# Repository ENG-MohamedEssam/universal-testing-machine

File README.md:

# universal-testing-machine

## **Abstract**
#### This projet at first was about Reverse-Engineering a Stress/Strain analysis machine, then fix it and Automate it's process.
#### The following is an image of the machine 

#### Every part of the machine was Reverse-Engineered from the boards to the hydraulics to the classic control.
#### The following is an image of one of the Reverse-Engineered boards which was mine to Reverese-Engineer.

#### I reverse Engineered The MV3058

#### Due to financial and permits issues the project was turned to be a prototype working with Embedded Systems.

#### The following is an image of the Prototype

#### The boards were desiged as follows, one board for the control, the second as a relay module. 

## **How the prototype works?**
 
#### The prototype mainly does exactly what the original machine does but on a smaller scale.
#### we mainly put a specimen between the two grippers and the machine puts tension or compression on the specimen till it breaks 
#### then it draws the Stress/Strain curves of the specimen's material.
#### It has a stepper motor used to adjust the place of the speciment, 
#### a piston that's derived by a hydraulic pump, 
#### a gripper used to grab the specimen.
#### As far as the Embedded systems part is concerend the machine had mainly 2 sensors ,
#### The Load Cell that's used to measure the Force and the Linear potentiometer that's used to measer the delta L.
#### the prototype is based mainly on two equations, Stress equation and Strain equation.
#### σ = F/A   ,    ε = δ/L  
#### the only two variables in these equations are the Force and the change in the length 

#### The following is images of the boards and panel.

#### The follwing is Single Line Diagram that was made by me , it'll give you a good overview of all the Hardware connections in the panel

#### The following link has some small SolidWorks parts that i've made for the machine whether it was as a specimen or for the sensors housings 
#### [parts](https://github.com/ENG-MohamedEssam/universal-testing-machine/tree/main/other-files/parts)

#### The following link has an explanation of the Embedded systems part explained by me 
#### [Explanation](https://drive.google.com/file/d/1bGaOVOjb-tQGSpPLI7ITkfYBf-VQDN8E/view)

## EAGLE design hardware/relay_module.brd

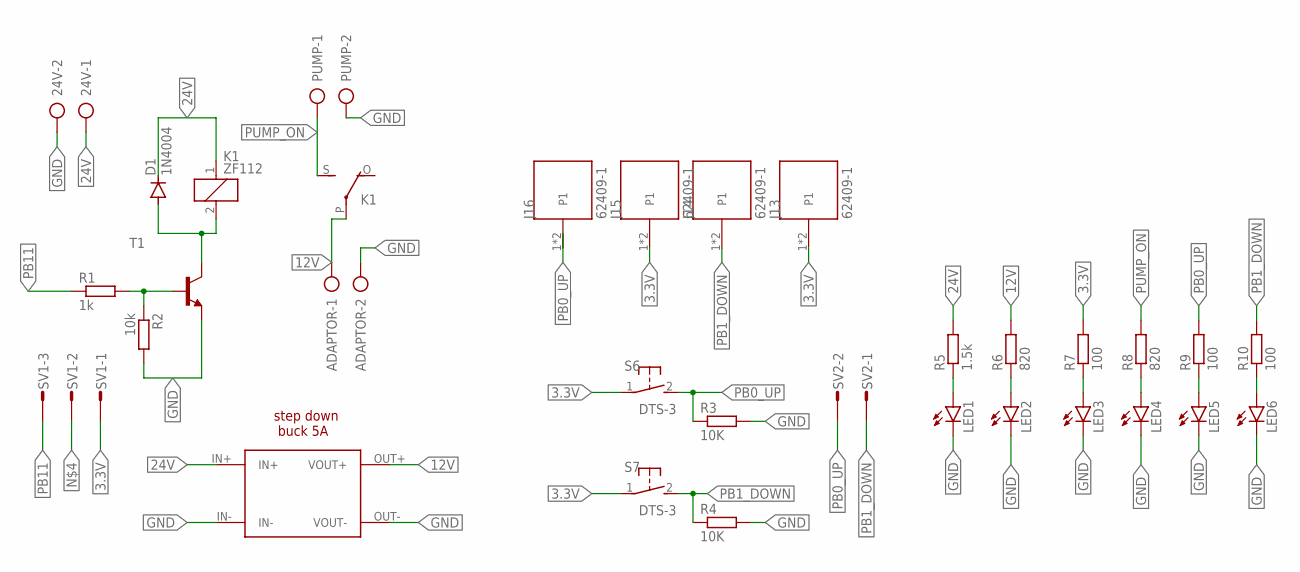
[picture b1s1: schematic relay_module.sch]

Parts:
24V: AK300/2
ADAPTOR: AK300/2
D1: 1N4004; DO41-10
J13, J14, J15, J16: 62409-1; TE_62409-1
K1: ZF112
LED1, LED2, LED3, LED4, LED5, LED6: LED5MM
PUMP: AK300/2
R1: 1k; 0204/7
R2: 10k; 0204/7
R3, R4: 10K; 0204/7
R5: 1.5k; 0204/7
R6, R8: 820; 0204/7
R7, R9, R10: 100; 0204/7
S6, S7: DTS-3
SV1: CON-AMP-MT_S03P
SV2: CON-AMP-MT_S02P
T1: 2N2222-NPN-TO92-EBC; TO92-EBC
U$1: BUCK_5A

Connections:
3.3V: J13.1, J13.2, J15.1, J15.2, R7.2, S6.1, S7.1, SV1.1
12V: ADAPTOR.1, K1.P, R6.2, U$1.OUT+ (VOUT+)
24V: 24V.1, D1.C, K1.1, R5.2, U$1.IN+
GND: 24V.2, ADAPTOR.2, LED1.K (C), LED2.K (C), LED3.K (C), LED4.K (C), LED5.K (C), LED6.K (C), PUMP.2, R2.2, R3.2, R4.2, T1.E, U$1.IN-, U$1.OUT- (VOUT-)
unnamed: R1.2, R2.1, T1.B
unnamed: LED1.A, R5.1
unnamed: D1.A, K1.2, T1.C
unnamed: LED2.A, R6.1
unnamed: LED5.A, R9.1
unnamed: LED3.A, R7.1
unnamed: LED4.A, R8.1
unnamed: LED6.A, R10.1
PB0_UP: J16.1, J16.2, R3.1, R9.2, S6.2, SV2.2
PB1_DOWN: J14.1, J14.2, R4.1, R10.2, S7.2, SV2.1
PB11: R1.1, SV1.3
PUMP_ON: K1.S, PUMP.1, R8.2

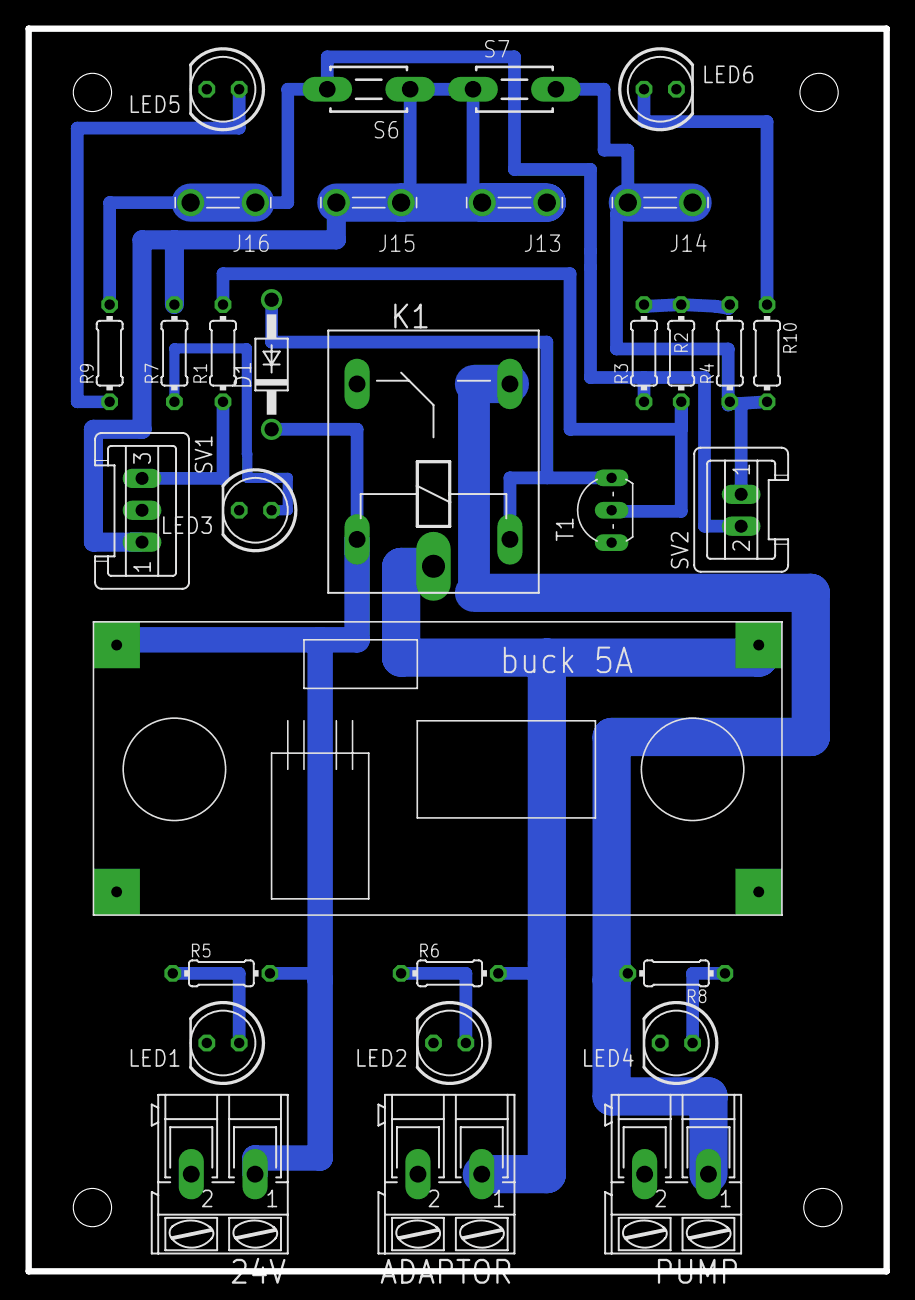
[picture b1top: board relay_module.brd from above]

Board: 2 copper layers, 67.3 x 97.5 mm, 31 parts (0 on the bottom side), 16 nets.

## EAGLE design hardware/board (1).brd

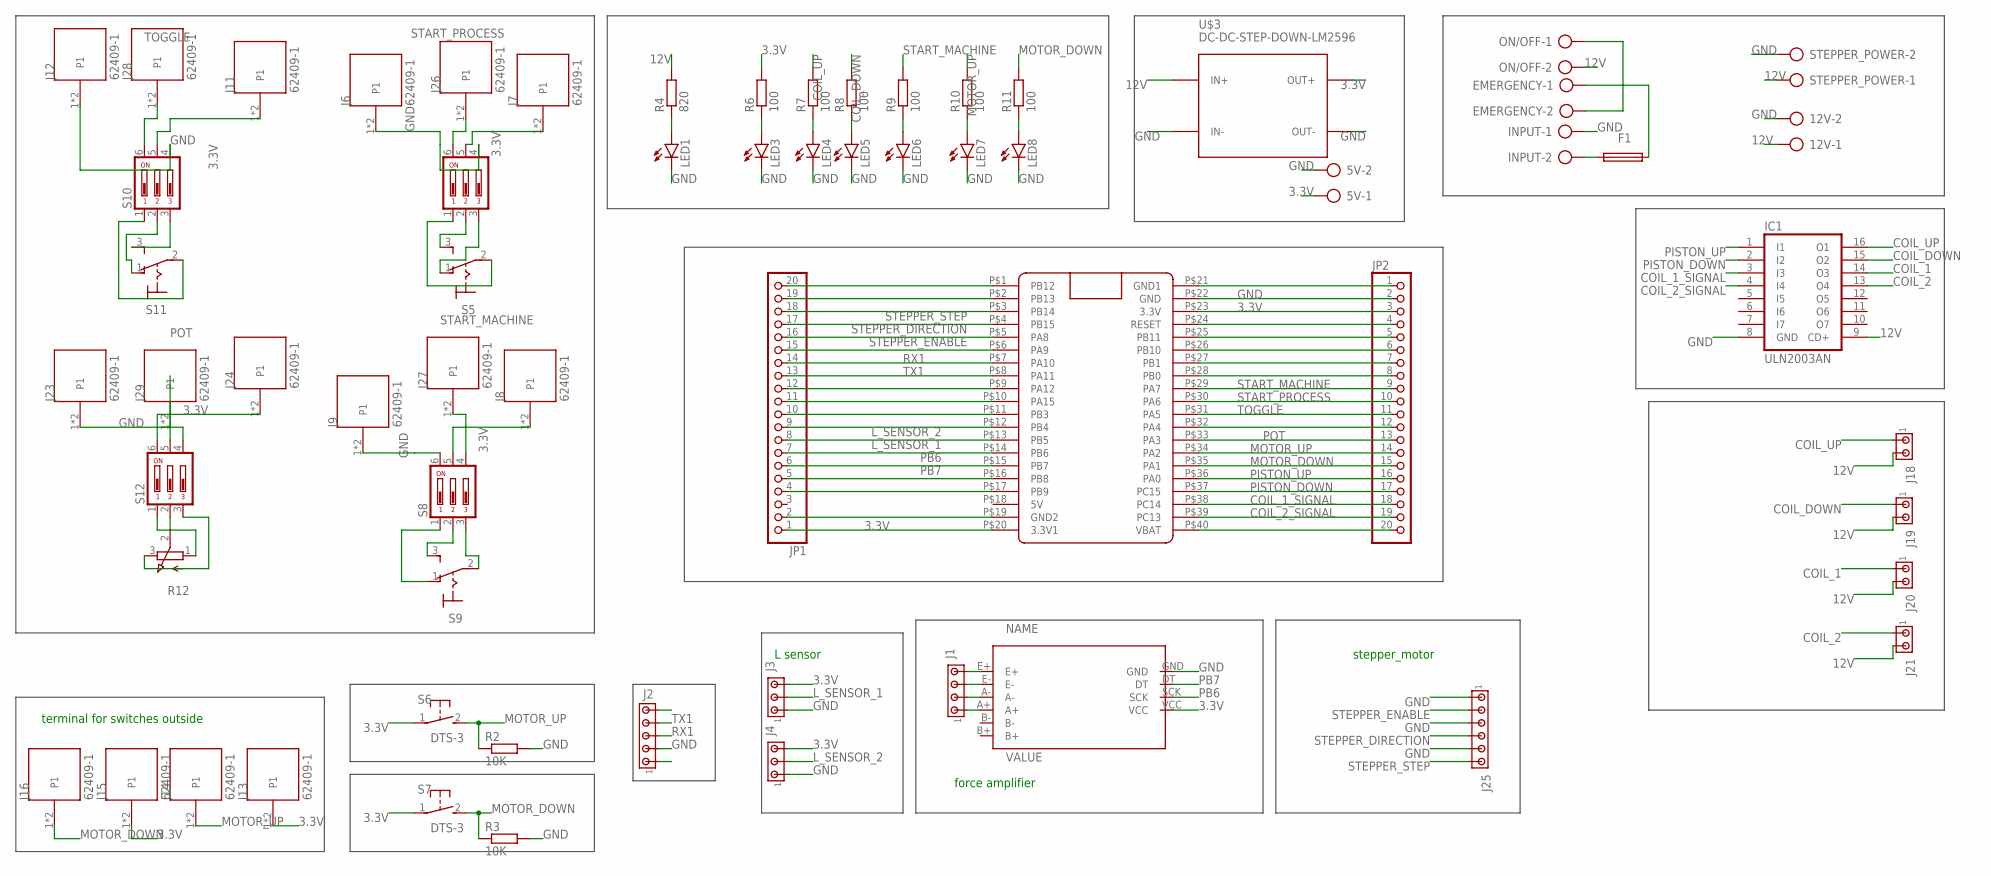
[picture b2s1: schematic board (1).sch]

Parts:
5V, 12V: AK300/2
EMERGENCY: AK300/2
F1: SH22
IC1: ULN2003AN; DIL16
INPUT: AK300/2
J1: MTA04-100; 10X04MTA
J2: MTA05-100; 10X05MTA
J3, J4: MTA03-100; 10X03MTA
J6, J7, J8, J9, J11, J12, J13, J14, J15, J16, J23, J24, J26, J27, J28, J29: 62409-1; TE_62409-1
J18, J19, J20, J21: MTA02-100; 10X02MTA
J25: MTA06-100; 10X06MTA
JP1, JP2: PINHD-1X20; 1X20
LED1, LED3, LED4, LED5, LED6, LED7, LED8: LED3MM
ON/OFF: AK300/2
R2, R3: 10K; 0204/7
R4: 820; 0204/7
R6, R7, R8, R9, R10, R11: 100; 0204/7
R12: 3RP/1610N
S4, S8, S10, S12: DP03; DP-03
S5, S9, S11: 320-916
S6, S7: DTS-3
STEPPER_POWER: AK300/2
U$1: BLUE_PILL
U$2: HX711A; HX711
U$3: DC-DC-STEP-DOWN-LM2596

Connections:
3.3V: 5V.1, J3.3, J4.3, J7.1, J7.2, J8.1, J8.2, J11.1, J11.2, J13.1, J13.2, J15.1, J15.2, J24.1, J24.2, JP1.1, JP2.3, R6.2, S4.5, S6.1, S7.1, S8.5, S10.5, S12.6, U$1.P$20 (3.3V1), U$1.P$23 (3.3V), U$2.VCC, U$3.OUT+
12V: 12V.1, IC1.9 (CD+), J18.2, J19.2, J20.2, J21.2, ON/OFF.2, R4.2, STEPPER_POWER.1, U$3.IN+
COIL_1: IC1.14 (O3), J20.1
COIL_1_SIGNAL: IC1.3 (I3), JP2.18, U$1.P$38 (PC14)
COIL_2: IC1.13 (O4), J21.1
COIL_2_SIGNAL: IC1.4 (I4), JP2.19, U$1.P$39 (PC13)
COIL_DOWN: IC1.15 (O2), J19.1, R8.2
COIL_UP: IC1.16 (O1), J18.1, R7.2
GND: 5V.2, 12V.2, IC1.8 (GND), INPUT.1, J2.2, J3.1, J4.1, J6.1, J6.2, J9.1, J9.2, J12.1, J12.2, J23.1, J23.2, J25.1, J25.3, J25.5, JP1.2, JP2.2, LED1.K (C), LED3.K (C), LED4.K (C), LED5.K (C), LED6.K (C), LED7.K (C), LED8.K (C), R2.2, R3.2, S4.4, S8.6, S10.4, S12.4, STEPPER_POWER.2, U$1.P$19 (GND2), U$1.P$22 (GND), U$2.GND, U$3.IN-, U$3.OUT-
L_SENSOR_1: J3.2, JP1.8, U$1.P$13 (PB5)
L_SENSOR_2: J4.2, JP1.9, U$1.P$12 (PB4)
MOTOR_DOWN: J16.1, J16.2, JP2.15, R3.1, R11.2, S7.2, U$1.P$35 (PA1)
MOTOR_UP: J14.1, J14.2, JP2.14, R2.1, R10.2, S6.2, U$1.P$34 (PA2)
unnamed: J1.4, U$2.E+
unnamed: J1.3, U$2.E-
unnamed: J1.2, U$2.A-
unnamed: J1.1, U$2.A+
unnamed: LED1.A, R4.1
unnamed: LED3.A, R6.1
unnamed: LED4.A, R7.1
unnamed: LED5.A, R8.1
unnamed: LED6.A, R9.1
unnamed: LED7.A, R10.1
unnamed: LED8.A, R11.1
unnamed: F1.1, INPUT.2
unnamed: S4.1, S5.2
unnamed: S4.2, S5.3 (S)
unnamed: JP1.4, U$1.P$17 (PB9)
unnamed: JP1.5, U$1.P$16 (PB8)
unnamed: JP1.10, U$1.P$11 (PB3)
unnamed: JP1.11, U$1.P$10 (PA15)
unnamed: JP1.12, U$1.P$9 (PA12)
unnamed: JP1.13, U$1.P$8 (PA11)
unnamed: EMERGENCY.1, F1.2
unnamed: EMERGENCY.2, ON/OFF.1
unnamed: JP2.20, U$1.P$40 (VBAT)
unnamed: JP2.7, U$1.P$27 (PB1)
unnamed: JP2.8, U$1.P$28 (PB0)
unnamed: JP1.20, U$1.P$1 (PB12)
unnamed: JP1.19, U$1.P$2 (PB13)
unnamed: S4.3, S5.1 (O)
unnamed: S10.1, S11.2
unnamed: S8.3, S9.2
unnamed: S8.1, S9.1 (O)
unnamed: JP2.1, U$1.P$21 (GND1)
unnamed: JP2.4, U$1.P$24 (RESET)
unnamed: S8.2, S9.3 (S)
unnamed: S10.3, S11.3 (S)
unnamed: S10.2, S11.1 (O)
unnamed: JP2.6, U$1.P$26 (PB10)
unnamed: R12.3 (E), S12.3
unnamed: R12.1 (A), S12.1
unnamed: R12.2 (S), S12.2
unnamed: JP2.12, U$1.P$32 (PA4)
unnamed: JP2.5, U$1.P$25 (PB11)
PB6: JP1.7, U$1.P$14 (PB6), U$2.SCK
PB7: JP1.6, U$1.P$15 (PB7), U$2.DT
PISTON_DOWN: IC1.2 (I2), JP2.17, U$1.P$37 (PC15)
PISTON_UP: IC1.1 (I1), JP2.16, U$1.P$36 (PA0)
POT: J29.1, J29.2, JP2.13, S12.5, U$1.P$33 (PA3)
RX1: J2.3, JP1.15, U$1.P$6 (PA9)
START_MACHINE: J27.1, J27.2, JP2.9, R9.2, S8.4, U$1.P$29 (PA7)
START_PROCESS: J26.1, J26.2, JP2.10, S4.6, U$1.P$30 (PA6)
STEPPER_DIRECTION: J25.4, JP1.17, U$1.P$4 (PB15)
STEPPER_ENABLE: J25.2, JP1.16, U$1.P$5 (PA8)
STEPPER_STEP: J25.6, JP1.18, U$1.P$3 (PB14)
TOGGLE: J28.1, J28.2, JP2.11, S10.6, U$1.P$31 (PA5)
TX1: J2.4, JP1.14, U$1.P$7 (PA10)

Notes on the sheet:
force amplifier
stepper_motor
L sensor
terminal for switches outside

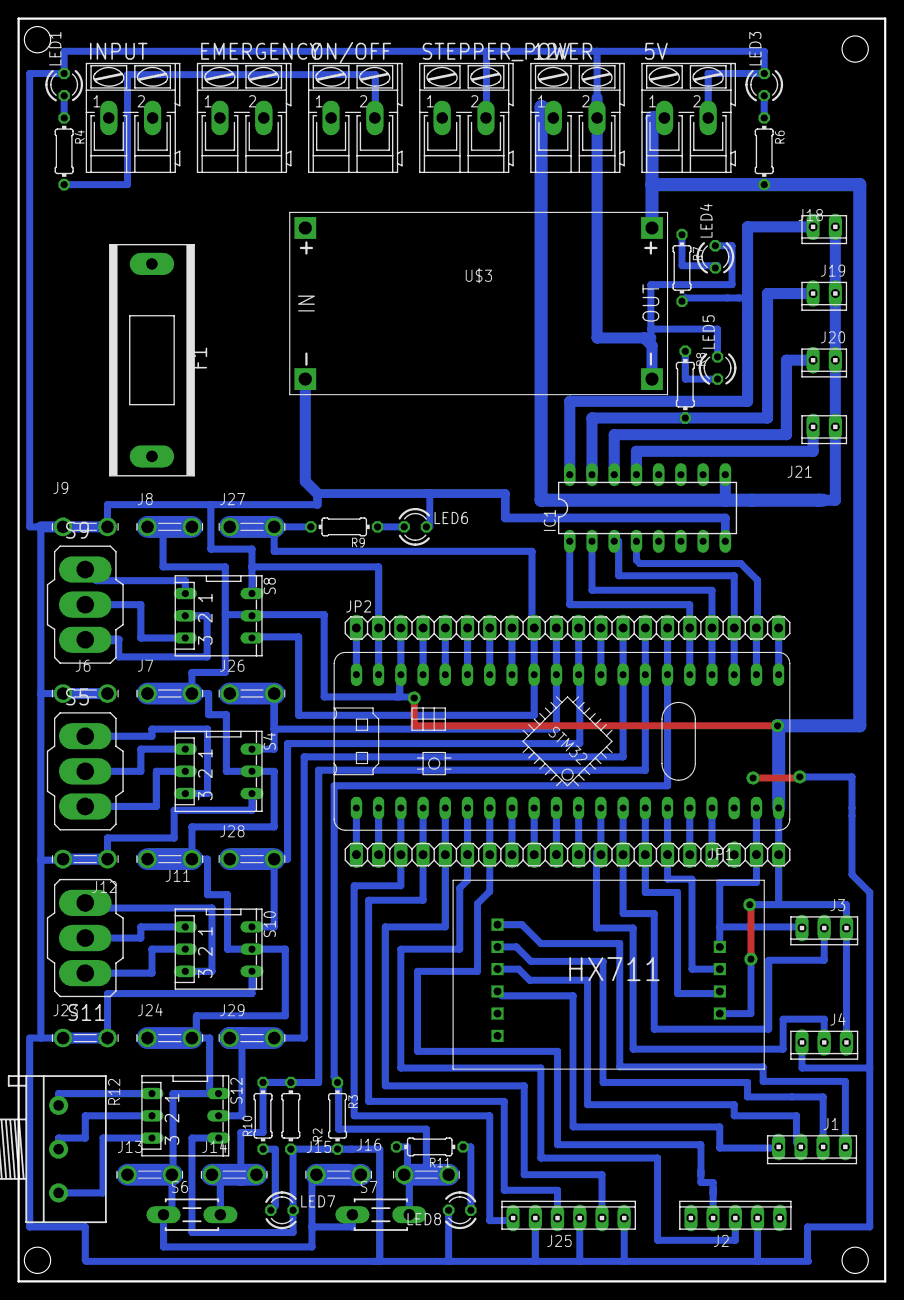
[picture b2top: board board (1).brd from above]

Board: 2 copper layers, 99.0 x 144.3 mm, 64 parts (0 on the bottom side), 68 nets.

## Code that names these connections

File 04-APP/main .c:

//*********************************************************************************/
/* Author    : Embedded system Sub team                                          */
/* Version   : V01                                                              */
/* Date      : 14 May 2020                                                     */
/******************************************************************************/

#include <stdio.h>
#include <stdlib.h>
#include "diag/Trace.h"


// Sample pragmas to cope with warnings. Please note the related line at
// the end of this function, used to pop the compiler diagnostics status.
#pragma GCC diagnostic push
#pragma GCC diagnostic ignored "-Wunused-parameter"
#pragma GCC diagnostic ignored "-Wmissing-declarations"
#pragma GCC diagnostic ignored "-Wreturn-type"
/******** includes Section **********/
#include "STD_TYPES.h"
#include "BIT_MATH.h"
#include "MCAL/RCC_interface.h"
#include "MCAL/DIO_interface.h"
#include "MCAL/USART_interface.h"
#include "MCAL/STK_interface.h"
#include "HAL/HX7111_force_sensor.h"
#include "HAL/STEPPER_HAL.h"
#include "MCAL/ADC_interface.h"
//------------------Macros---------
#define START_M             PIN7               // On or high (Toggle)     GPIOA
#define MOTOR_UP            PIN2               // normal push button      GPIOA
#define MOTOR_DOWN          PIN1               // normal push button      GPIOA
#define START_PROCESS       PIN6               //Toggle                   GPIOA
#define TOGGLE              PIN5               // tension or compression  GPIOA
#define PUMB_UP             PIN1               // pump (port B)
#define PUMB_DWON           PIN2               // pump (port B)
//-----------------------------
#define PISTON_UP      PIN0
#define PISTON_DOWN    PIN10
/*************************************/
//-----------------global variables -------
extern u8 global_u8ReceivedData;
float force;
float DeltaLength;
float Area = 125;   //mm2
float length = 70;   // meter
float Stress;
float Strain;
u8 X_axis[100];
u8 Y_axis[100];
int Gcount=0;
char breakpoint = 0;
char val1=0;
u8 flag=0;
/************************************/


/******************* Functions *********************/
void Fault_fun(void)
{
//	TOG_BIT(flag , 0);
//	MGPIO_VidSetPinValue(GPIOA,PIN10,flag);

}

void adjustmotor_UP()
{
	if(MGPIO_u8GetPinValue ( GPIOA , MOTOR_UP))
	{
		STEPPER_FORWARD(GPIOB, PIN14, GPIOB, PIN15,5000); //range time delay from 50 to 1000
	}

	else
	{
		STEPPER_stop(GPIOB, PIN14, GPIOB, PIN15);
	}
}


void adjustmotor_DOWN()
{

   if(MGPIO_u8GetPinValue ( GPIOA , MOTOR_DOWN))
	{
		STEPPER_REVERSE(GPIOB, PIN14, GPIOB, PIN15,5000);
	}
	else
	{
		STEPPER_stop(GPIOB, PIN14, GPIOB, PIN15);
	}
}


void selnoid_UP(){
 	MGPIO_VidSetPinValue(GPIOB, PISTON_UP, HIGH);
    MGPIO_VidSetPinValue(GPIOB, PISTON_DOWN, LOW);
    MSTK_voidSetBusyWait(300000);// 0.3 sec
 	MGPIO_VidSetPinValue(GPIOB, PISTON_UP, LOW);
    MGPIO_VidSetPinValue(GPIOB, PISTON_DOWN, LOW);
}
void selnoid_DWON(){
 	MGPIO_VidSetPinValue(GPIOB, PISTON_UP, LOW);
    MGPIO_VidSetPinValue(GPIOB, PISTON_DOWN, HIGH);
    MSTK_voidSetBusyWait(300000);// 0.3 sec
 	MGPIO_VidSetPinValue(GPIOB, PISTON_UP, LOW);
    MGPIO_VidSetPinValue(GPIOB, PISTON_DOWN, LOW);
}

void switches_int(void)
{

	MGPIO_VidSetPinDirection(GPIOA,START_M,INPUT_FLOATING);
	MGPIO_VidSetPinDirection(GPIOA,MOTOR_UP,INPUT_FLOATING);
	MGPIO_VidSetPinDirection(GPIOA,MOTOR_DOWN,INPUT_FLOATING);
	MGPIO_VidSetPinDirection(GPIOA,START_PROCESS,INPUT_FLOATING);
	MGPIO_VidSetPinDirection(GPIOA,TOGGLE,INPUT_FLOATING);

	MGPIO_VidSetPinDirection(GPIOA,PUMB_UP,INPUT_FLOATING);// NEW: port B
	MGPIO_VidSetPinDirection(GPIOA,PUMB_DWON,INPUT_FLOATING);

	MGPIO_VidSetPinDirection(GPIOA,PISTON_UP,OUTPUT_SPEED_10MHZ_PP); //for  pump Up
	MGPIO_VidSetPinDirection(GPIOB,PISTON_DOWN,OUTPUT_SPEED_10MHZ_PP);//for pump down

}

void Compression ()
{  	MGPIO_VidSetPinValue(GPIOB, PISTON_UP, HIGH);
MGPIO_VidSetPinValue(GPIOB, PISTON_DOWN, LOW);
MSTK_voidSetBusyWait(100);
force = ADC_u16ReadChannelPoll(1);
while(force>10 && MGPIO_u8GetPinValue(GPIOA,TOGGLE))
{

	force = ADC_u16ReadChannelPoll(1);
	DeltaLength = ADC_u16ReadChannelPoll(4);
	Stress  = force / Area;  //stress eqn
	Strain  = DeltaLength / length; // srain eqn
	X_axis[Gcount] = (char) Stress * 10;             //i.e. 1.4*10 = 14
	Y_axis[Gcount] = (char) Strain * 10;
	Gcount++;
}
for(int i=0; i<=Gcount; i++){
	MUSART1_voidTransmit(&X_axis[i],1);
	MUSART1_voidTransmit(&Y_axis[i],1);
}
Gcount =0 ;
breakpoint = 1;
}


void Tension(void)
{
	MGPIO_VidSetPinValue(GPIOB, PISTON_UP, LOW);
	MGPIO_VidSetPinValue(GPIOB, PISTON_DOWN, HIGH);
	MSTK_voidSetBusyWait(100);
	force = ADC_u16ReadChannelPoll(1);
	while(force>10 && MGPIO_u8GetPinValue(GPIOA,TOGGLE))
	{

		force = ADC_u16ReadChannelPoll(1);
		DeltaLength = ADC_u16ReadChannelPoll(4);
		Stress  = force / Area;  //stress eqn
		Strain  = DeltaLength / length; // srain eqn
		X_axis[Gcount] = (char) Stress * 10;             //i.e. 1.4*10 = 14
		Y_axis[Gcount] = (char) Strain * 10;
		Gcount++;
	}
	for(int i=0; i<=Gcount; i++){
		MUSART1_voidTransmit(&X_axis[i],1);
		MUSART1_voidTransmit(&Y_axis[i],1);
	}
	Gcount =0 ;
	breakpoint = 1;

}



int main(int argc, char* argv[])
{

	// init preigherals and clocks

	RCC_voidInitSysClock();
	RCC_voidEnableClock(RCC_APB2,2);  // clocks for port A
	RCC_voidEnableClock(RCC_APB2,3);  // clocks for port B
	RCC_voidEnableClock(RCC_APB2,9);  // clocks for ADC1
	RCC_voidEnableClock(RCC_APB2,14); // clocks for UART1
	MSTK_voidInit();
	ADC_VoidInit();
	MUSART1_voidInit();
	//--------------------------------
	/* Setting A9:TX pin as Output alternate function push pull w max speed 50 MHz */
	MGPIO_VidSetPinDirection(GPIOA,PIN9,OUTPUT_SPEED_50MHZ_AFPP);
	/* Setting A10:RX pin as input floating */
	MGPIO_VidSetPinDirection(GPIOA,PIN10,OUTPUT_SPEED_2MHZ_PP);
	STEPPER_void_init(GPIOB,PIN14,GPIOB,PIN15);
    switches_int();
	MUSART1_voidSetcallBack(Fault_fun);
	u8 Recive_USART=0;
	while(1)
	{
		if(MGPIO_u8GetPinValue(GPIOA,START_M)){



			if(MGPIO_u8GetPinValue(GPIOA,MOTOR_UP) || global_u8ReceivedData == 1U ){

				adjustmotor_UP();
			}
			else if(MGPIO_u8GetPinValue(GPIOA,MOTOR_DOWN) || global_u8ReceivedData == 2U){

				adjustmotor_DOWN();
			}
			else if(MGPIO_u8GetPinValue(GPIOA,PUMB_UP) || global_u8ReceivedData == 3U){

				selnoid_UP();
			}
			else if(MGPIO_u8GetPinValue(GPIOA,PUMB_DWON) || global_u8ReceivedData == 4U){

				selnoid_DWON();
			}
			else if(MGPIO_u8GetPinValue(GPIOA,TOGGLE) || global_u8ReceivedData == 5U){   //Say compression

				Compression();
			}
			else if(!MGPIO_u8GetPinValue(GPIOA,TOGGLE) || global_u8ReceivedData == 6U){   //Say tension

					Tension();
			}

			else {
                   //Do nothing
			}





		}

	}



}
#pragma GCC diagnostic pop

//
// Recive_USART = MUSART1_u8Receive();
//		switch(Recive_USART){
//		case 1:
//			adjustmotor_UP();    // Move Stepper motor Up
//			break;
//		case 2:
//			adjustmotor_DWON();  // Move Stepper motor Up
//			break;
//		case 3:
//			break;
//		case 4:
//			break;
//		case 5:
//			break;
//
//
//
//
//
//	     	}

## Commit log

2022-12-05 Update README.md
    Test markup
2022-12-05 Test
2022-12-05 Update README.md
    Test
2022-12-05 Update README.md
    Test image in markup
2022-12-05 Update README.md
    First commit of the project explanation, (just an intro)
2022-12-05 Updating the images and some text in readme
2022-12-05 Edit in the image links
2022-12-05 Some Edits in the text and images
2022-12-05 Uploading SolidWorks parts and editing the readme file
2022-12-05 small edit in a link in readme file
2022-12-07 Edit in readme

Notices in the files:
parts and their libraries:
buck 3A: Released under the Creative Commons Attribution 4.0 International License: http://creativecommons.org/licenses/by/4.0
